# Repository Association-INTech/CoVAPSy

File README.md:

# CoVAPSy - AutoTech Project

AutoTech is a project from the INTech robotics club (Telecom SudParis and IMT Business School). Our goal is to design and build an autonomous vehicle for [CoVAPSy](https://ajuton-ens.github.io/CourseVoituresAutonomesSaclay/) (Course de Voitures Autonomes de Paris-Saclay) competition.

This repository contains the source code for our autonomous vehicle for the 2025 and 2026 competitions.

## Our Approach

We chose to use a full Reinforcement Learning approach. We train an agent to drive the vehicle in a simulation of the race based directly on sensor inputs.

We train the AI model in parallel remote environments through nammed pipes connections between the main python script and the multiple webots instances.

Inside the simulations, each vehicle has access to data comming from a LiDAR and a camera.

- Simulator: [Webots](https://cyberbotics.com/)
- AI Training Library: [Stable-Baselines3](https://stable-baselines3.readthedocs.io/en/master/) with a [Pytorch](https://pytorch.org/) backend
- AI Inference Engine: [ONNX](https://onnx.ai/)

## Installation

We use uv for Python environment management. So if it's not already installed go check the [official installation guide](https://docs.astral.sh/uv/getting-started/installation/)

Then, just `uv sync` to create the virtual environment and get all the dependencies.
```bash
# dependencies for AI training
uv sync --extra simu

# dependencies for AI inference on the Raspberry PI 5
uv sync --extra rpi
```

## Training usage

Navigate to the simulator directory.
```bash
cd src/Simulateur
```

Run the multi-process training script.
```bash
uv run launch_train_multiprocessing.py
```
This will launch the Webots instances and begin the SB3 PPO training loop. All the checkpoints will be in the `checkpoints` directory. At every checkpoint, a compiled ONNX model will be stored as `model.onnx`.

To change the parameters of the simulation, just modify the `config.py` file.

## Inference usage

(WIP)

# Wiki (Documentation)

For detailed information on architecture, hardware specifics and technical choices, please refer to the [INTech wiki](https://wiki.intech-robotics.fr).

(Note: The Wiki is currently private and reserved to INTech members)

# some dependencies needed 
libcap-dev
python3-libcamera

# License

This project is distributed under the MIT License. See the Licence file for details.

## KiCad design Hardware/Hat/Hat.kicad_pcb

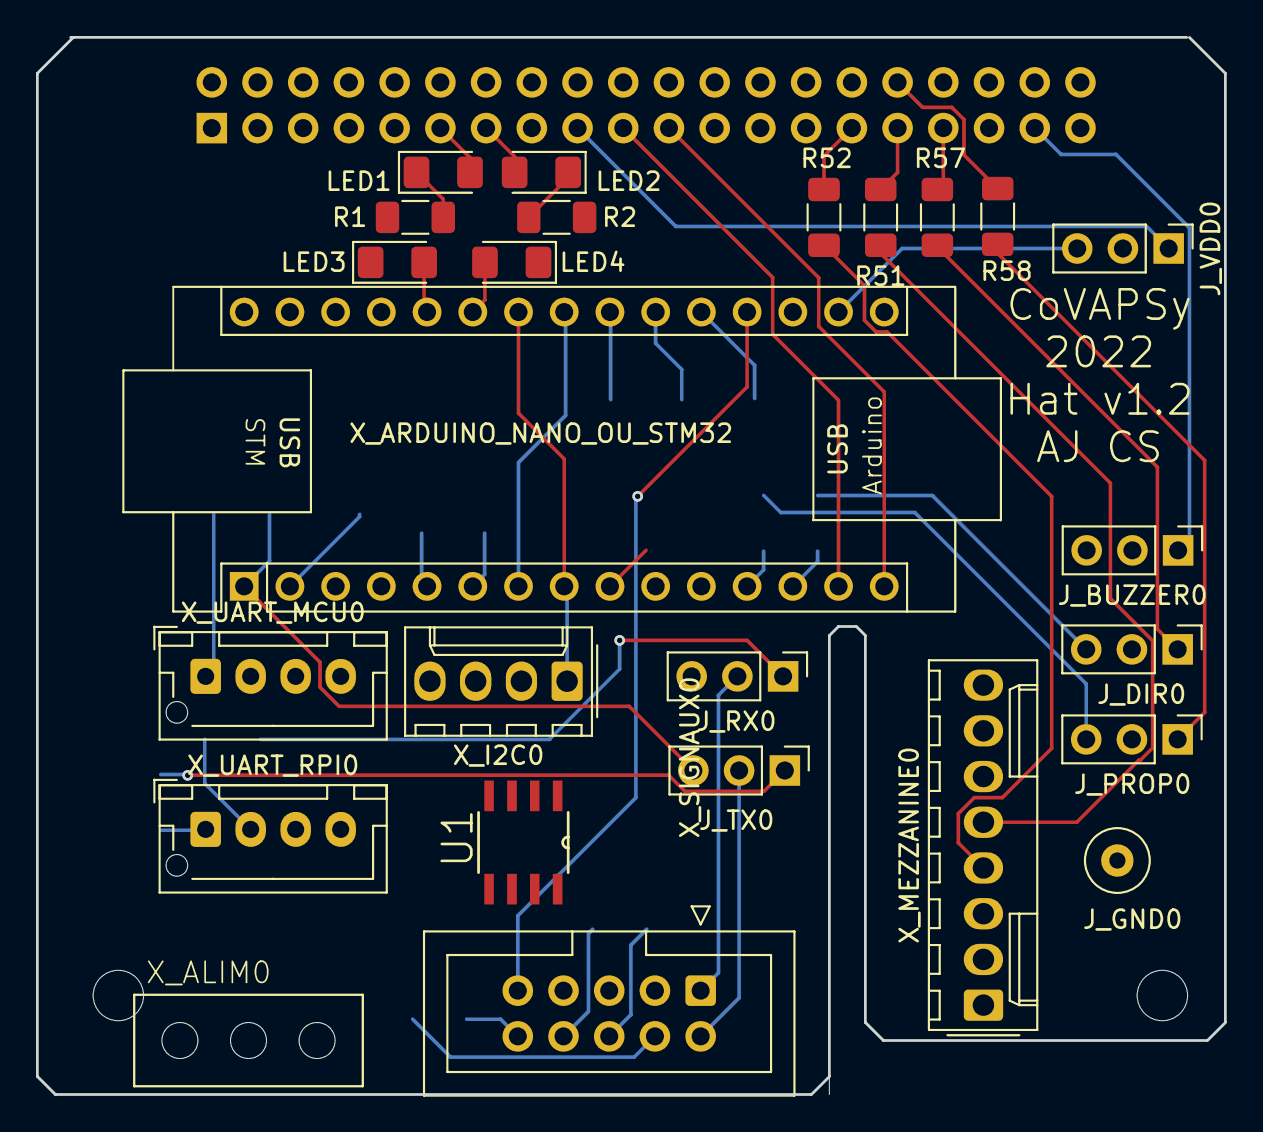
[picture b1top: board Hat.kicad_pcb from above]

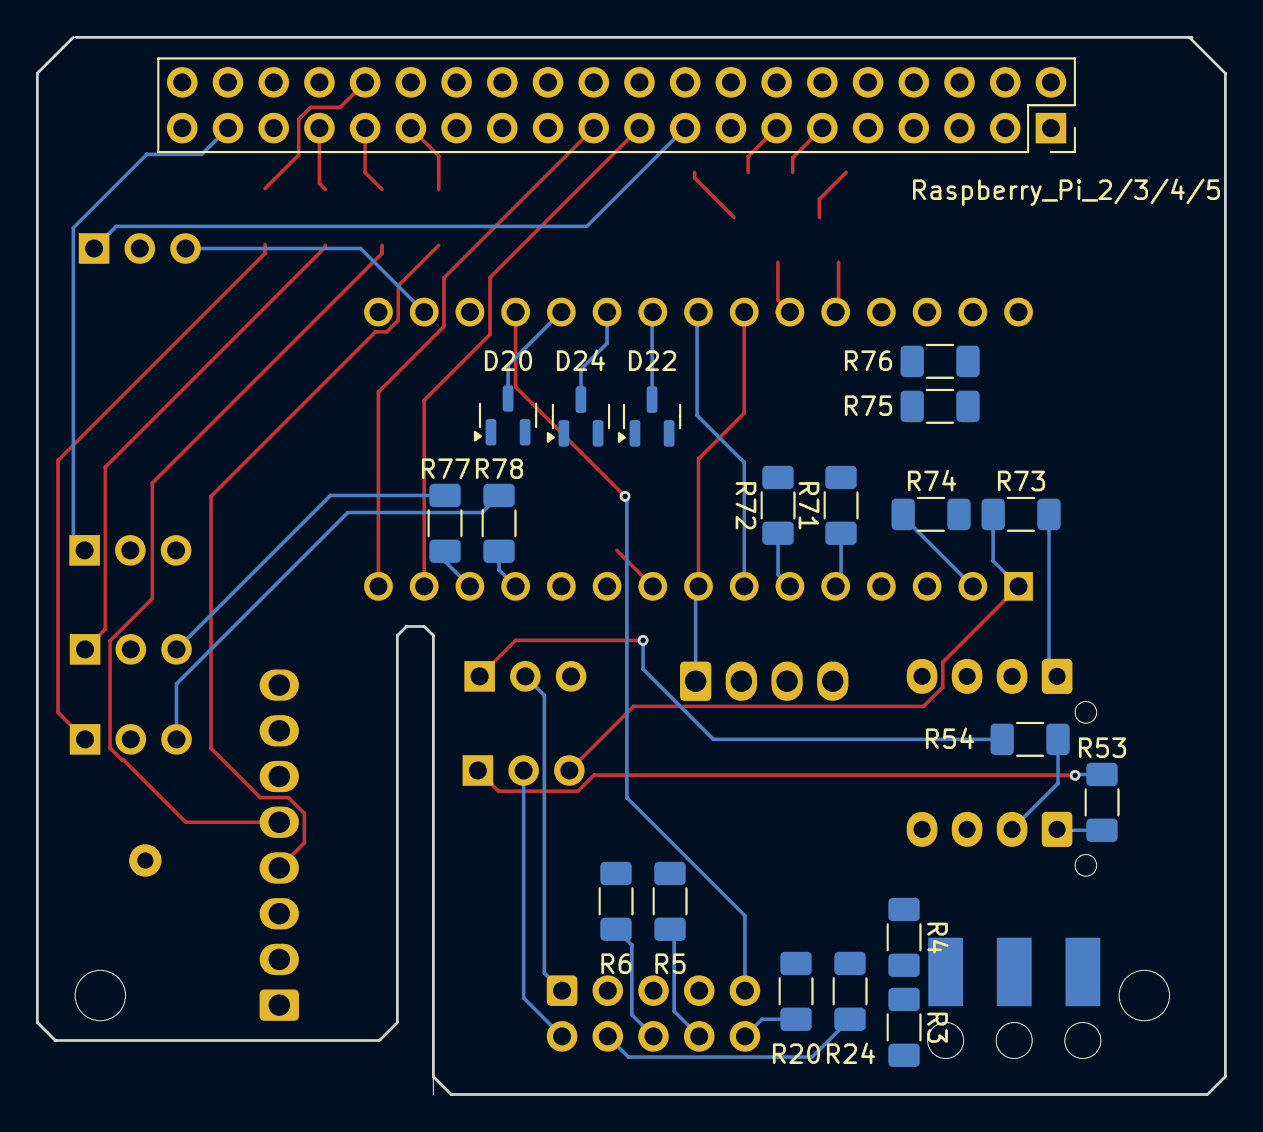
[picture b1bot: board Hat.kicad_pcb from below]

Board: 2 copper layers, 66.0 x 58.7 mm, 47 parts (20 on the bottom side), 56 nets.

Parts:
@HOLE0, @HOLE1: (no value)
D20, D22, D24: BAT54S; SOT-23
J_BUZZER0: Jumper_3_Open; PinHeader_1x03_P2.54mm_Vertical
J_DIR0: Jumper_3_Open; PinHeader_1x03_P2.54mm_Vertical
J_GND0: TestPoint; TestPoint_Loop_D3.50mm_Drill0.9mm_Beaded
J_PROP0: Jumper_3_Open; PinHeader_1x03_P2.54mm_Vertical
J_RX0: Jumper_3_Open; PinHeader_1x03_P2.54mm_Vertical
J_TX0: Jumper_3_Open; PinHeader_1x03_P2.54mm_Vertical
J_VDD0: Jumper_3_Open; PinHeader_1x03_P2.54mm_Vertical
LED1, LED2, LED3, LED4: LEDSML1206; D_1206_3216Metric_Pad1.42x1.75mm_HandSolder
R1, R2, R3, R20, R24, R51, R52, R53, R54, R57, R58, R71, R72, R73, R74, R75, R76, R77, R78: 560; R_1206_3216Metric_Pad1.30x1.75mm_HandSolder
R4: 1k; R_1206_3216Metric_Pad1.30x1.75mm_HandSolder
R5, R6: 4.7k; R_1206_3216Metric_Pad1.30x1.75mm_HandSolder
Raspberry_Pi_2/3/4/5: Conn_02x20; PinHeader_2x20_P2.54mm_Vertical
U1: PCA9517D; SOIC127P600X175-8N
X_ALIM0: CONN_ALIM_3TROUS
X_ARDUINO_NANO_OU_STM32: ARDUINO_NANO_STM32_NUCLEO; Arduino_Nano
X_I2C0: Conn_01x04; Molex_KK-254_AE-6410-04A_1x04_P2.54mm_Vertical
X_MEZZANINE0: Molex_KK-254_AE-6410-08A_1x08_P2.54mm_Vertical
X_SIGNAUX0: Conn_02x05; IDC-Header_2x05_P2.54mm_Vertical
X_UART_MCU0: Conn_01x04; JST_XH_B4B-XH-AM_1x04_P2.50mm_Vertical
X_UART_RPI0: Conn_01x04; JST_XH_B4B-XH-AM_1x04_P2.50mm_Vertical

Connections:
/BP1: R52.2, R71.2, X_MEZZANINE0.4
/BP2: R51.2, R72.2, X_MEZZANINE0.5
/BUZZER: J_BUZZER0.2 (C), X_MEZZANINE0.8
/BUZZER_MCU: J_BUZZER0.3 (B), X_ARDUINO_NANO_OU_STM32.9 (D6)
/BUZZER_RPI: J_BUZZER0.1 (A), Raspberry_Pi_2/3/4/5.37 (GPIO26)
/CAPT_IR_G: D20.3 (COM), R20.2, X_ARDUINO_NANO_OU_STM32.20 (A1)
/FOURCHE: X_ARDUINO_NANO_OU_STM32.19 (A0), X_SIGNAUX0.9
/I2C_SCL: Raspberry_Pi_2/3/4/5.5 (SCL/GPIO3), U1.2 (SCLA), X_ARDUINO_NANO_OU_STM32.8 (D5), X_ARDUINO_NANO_OU_STM32.24 (A5), X_I2C0.1, X_MEZZANINE0.3
/I2C_SCL_5V: R6.2, U1.7 (SCLB), X_SIGNAUX0.6
/I2C_SDA: Raspberry_Pi_2/3/4/5.3 (SDA/GPIO2), U1.3 (SDAA), X_ARDUINO_NANO_OU_STM32.7 (D4), X_ARDUINO_NANO_OU_STM32.23 (A4), X_I2C0.2, X_MEZZANINE0.2
/I2C_SDA_5V: R5.1, U1.6 (SDAB), X_SIGNAUX0.8
/MESURE_VBAT_LiPo: D24.3 (COM), R24.1, R24.2, X_ARDUINO_NANO_OU_STM32.21 (A2), X_SIGNAUX0.4
/MESURE_VBAT_NiMH: D22.3 (COM), X_ARDUINO_NANO_OU_STM32.22 (A3)
/MISO: Raspberry_Pi_2/3/4/5.21 (MISO0/GPIO9), X_ARDUINO_NANO_OU_STM32.15 (D12)
/MOSI: Raspberry_Pi_2/3/4/5.19 (MOSI0/GPIO10), X_ARDUINO_NANO_OU_STM32.14 (D11)
/PROPULSION_MCU: J_PROP0.3 (B), R78.2
/PROPULSION_RPI: J_PROP0.1 (A), R58.2
/PWM_DIRECTION: J_DIR0.2 (C), X_SIGNAUX0.5
/PWM_PROPULSION: J_PROP0.2 (C), X_SIGNAUX0.3
/RESET: X_ARDUINO_NANO_OU_STM32.3 (~RESET), X_MEZZANINE0.6
/RX_DIR: J_RX0.2 (C), X_SIGNAUX0.1
/RX_MCU: J_RX0.3 (B), R74.1, X_ARDUINO_NANO_OU_STM32.2 (D0/RX)
/RX_MCU_P: R74.2, X_UART_MCU0.2
/RX_RPI: J_RX0.1 (A), R54.1, Raspberry_Pi_2/3/4/5.10 (GPIO15/RXD)
/RX_RPI_P: R54.2, X_UART_RPI0.2
/SCK: Raspberry_Pi_2/3/4/5.23 (SCLK0/GPIO11), X_ARDUINO_NANO_OU_STM32.16 (D13)
/SERVO_DIR_MCU: J_DIR0.3 (B), R77.2
/SERVO_DIR_RPI: J_DIR0.1 (A), R57.2
/TELEM_G: R20.1, X_SIGNAUX0.10
/TX_DIR: J_TX0.2 (C), X_SIGNAUX0.2
/TX_MCU: J_TX0.3 (B), R73.1, X_ARDUINO_NANO_OU_STM32.1 (D1/TX)
/TX_MCU_P: R73.2, X_UART_MCU0.1
/TX_RPI: J_TX0.1 (A), R53.1, Raspberry_Pi_2/3/4/5.8 (GPIO14/TXD)
/TX_RPI_P: R53.2, X_UART_RPI0.1
/VCC_5V: R5.2, R6.1, Raspberry_Pi_2/3/4/5.2 (5V), Raspberry_Pi_2/3/4/5.4 (5V), U1.8 (VCCB), X_ARDUINO_NANO_OU_STM32.27 (+5V)
/VDD_MCU: J_VDD0.3 (B), X_ARDUINO_NANO_OU_STM32.17 (3V3)
/VDD_RPI: J_VDD0.1 (A), Raspberry_Pi_2/3/4/5.17 (3V3)
GND: D20.1 (A), D22.1 (A), D24.1 (A), J_GND0.1, R1.2, R2.2, R3.2, R75.2, R76.2, Raspberry_Pi_2/3/4/5.6 (GND), Raspberry_Pi_2/3/4/5.9 (GND), Raspberry_Pi_2/3/4/5.14 (GND), Raspberry_Pi_2/3/4/5.20 (GND), Raspberry_Pi_2/3/4/5.25 (GND), Raspberry_Pi_2/3/4/5.30 (GND), Raspberry_Pi_2/3/4/5.34 (GND), Raspberry_Pi_2/3/4/5.39 (GND), U1.4 (GND), X_ALIM0.P$2, X_ARDUINO_NANO_OU_STM32.4 (GND), X_ARDUINO_NANO_OU_STM32.29 (GND), X_I2C0.4, X_MEZZANINE0.7, X_UART_MCU0.3, X_UART_RPI0.3
unnamed: LED1.2 (A), Raspberry_Pi_2/3/4/5.11 (GPIO17)
unnamed: LED1.1 (K), R1.1
unnamed: LED2.2 (A), Raspberry_Pi_2/3/4/5.13 (GPIO27)
unnamed: LED2.1 (K), R2.1
unnamed: LED3.2 (A), X_ARDUINO_NANO_OU_STM32.26 (A7)
unnamed: LED3.1 (K), R76.1
unnamed: LED4.2 (A), X_ARDUINO_NANO_OU_STM32.25 (A6)
unnamed: LED4.1 (K), R75.1
unnamed: R3.1, R4.2
unnamed: R52.1, Raspberry_Pi_2/3/4/5.29 (GCLK1/GPIO5)
unnamed: R51.1, Raspberry_Pi_2/3/4/5.31 (GCLK2/GPIO6)
unnamed: R58.1, Raspberry_Pi_2/3/4/5.32 (PWM0/GPIO12)
unnamed: R57.1, Raspberry_Pi_2/3/4/5.33 (PWM1/GPIO13)
unnamed: R71.1, X_ARDUINO_NANO_OU_STM32.5 (D2)
unnamed: R72.1, X_ARDUINO_NANO_OU_STM32.6 (D3)
unnamed: R78.1, X_ARDUINO_NANO_OU_STM32.12 (D9)
unnamed: R77.1, X_ARDUINO_NANO_OU_STM32.13 (D10)
VDD: D20.2 (K), D22.2 (K), D24.2 (K), J_VDD0.2 (C), U1.1 (VCCA), X_I2C0.3, X_MEZZANINE0.1, X_SIGNAUX0.7, X_UART_MCU0.4, X_UART_RPI0.4

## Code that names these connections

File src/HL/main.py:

# States
# 0 - Idle
# 1 - Auto Driving
# 2 - Manual Driving with ps4 controller

from gpiozero import LED, Button, Buzzer
from luma.core.interface.serial import i2c
from luma.core.render import canvas
from luma.oled.device import ssd1306
from PIL import Image, ImageDraw, ImageFont
import struct
import smbus  # type: ignore #ignore the module could not be resolved error because it is a linux only module
import textwrap

from get_ip import get_ip, check_ssh_connections

from multiprocessing import Processus #pour pouvoir lancer les programme sur un cpu différent

bus = smbus.SMBus(1)  # 1 indicates /dev/i2c-1
#oled
serial = i2c(port=1, address=0x3C)
device = ssd1306(serial)

auto_driving_p = Process(target=Auto_Driving)
manual_driving_p = Process(target=Manual_Driving)

list_p = [auto_driving_p,manual_driving_p] #liste tout les processus possible

SLAVE_ADDRESS = 0x08  # I2C address of the slave arduino or stm32
bp_next = Button("GPIO5", bounce_time=0.1)
bp_entre = Button("GPIO6", bounce_time=0.1)
led1 = LED("GPIO17")
led2 = LED("GPIO27")
buzzer = Buzzer("GPIO26")
State = 0
Screen = 0
TEXT_HEIGHT = 11
TEXT_LEFT_OFFSET = 3 # Offset from the left of the screen to ensure no cuttoff


def make_voltage_im():
    try: #Will fail if arduino is rest ex: temporary power loss when plugu=ing in usb
        received = read_data(2)  # Adjust length as needed
    except OSError:
        received = [0.0, 0.0]
        print("I2C bus error")
    
    # filter out values below 6V and round to 2 decimal places
    received = [round(elem, 2) if elem > 6 else 0.0 for elem in received]
    text = f"LiP:{received[0]:.2f}V|NiH:{received[1]:.2f}V"
    im = Image.new("1", (128, TEXT_HEIGHT), "black")
    draw = ImageDraw.Draw(im)
    font = ImageFont.load_default()
    draw.text((3, 0), text, fill="white", font=font)
    return im

def display_combined_im(text):
    im = Image.new("1", (128, 64), "black")
    draw = ImageDraw.Draw(im)
    font = ImageFont.load_default()
    
    # Wrap the text to fit within the width of the display
    wrapped_text = textwrap.fill(text, width=20)  # Adjust width as needed
    draw.text((3, 0), wrapped_text, fill="white", font=font)
    
    voltage_im = make_voltage_im()
    im.paste(voltage_im, (0, 64 - TEXT_HEIGHT))
    
    with canvas(device) as draw:
        draw.bitmap((0, 0), im, fill="white")

def write_data(float_data):
    # Convert the float to bytes
    print(float_data)
    byte_data = struct.pack('f', float_data)
    # Convert the bytes to a list of integers
    int_data = list(byte_data)
    print(int_data)
    int_data.append(0)
    # Write the data to the I2C bus
    bus.write_i2c_block_data(SLAVE_ADDRESS, int_data[0], int_data[1:4])

def read_data(num_floats=3):

    # Each float is 4 bytes
    length = num_floats * 4
    # Read a block of data from the slave
    data = bus.read_i2c_block_data(SLAVE_ADDRESS, 0, length)
    # Convert the byte data to floats
    if len(data) >= length:
        float_values = struct.unpack('f' * num_floats, bytes(data[:length]))
        return list(float_values)
    else:
        raise ValueError("Not enough data received from I2C bus")


def Idle(): #Enable chossing between states
    global Screen
    global State
    if Screen==0 and check_ssh_connections():
        led1.on()
        Screen=1
    if not check_ssh_connections():
        led1.off()
    match Screen: #Display on OLED
        case 0: #IP and ssh status
            ip=get_ip()
            text = "Ready to SSH\nIP:"+ip
        case 1: #AutoDriving mode
            text = "Auto Driving"
        case 2: #Manual Driving mode
            text = "Manual Driving With PS4 Controller"
            #PS4 controller status
        case 3: #Kill all processus
            text = "Kill all the process"
    
    if (State==Screen):
        text+=": (en cours)"

    display_combined_im(text)


    if bp_next.is_pressed:
        bp_next.wait_for_release()
        Screen+=1
        if Screen>len(list_p):
            Screen=0
    if bp_entre.is_pressed:
        bp_entre.wait_for_release() 
        State=Screen
        p_choisie(State-1) # -1 because of the process cases begin at 1 and the list_p indexe at 0

def p_choisie(p_id):
    """ Kill tout les processus et lance celui choisie par p_id dans la liste list_p
        (Donner un p_id plus grand que len(list_p) tue tout les processus
    """
    for i in range(len(list_p)):
        if (i!= p_id):
            list_p[i].terminate()

    if (p_id<len(list_p)): #vérifie que le p_id soit valide dans
        if not list_[p_id].is_alive(): #evite de relancer le programme si déjà selectionée
            list_p[p_id].start()


def Auto_Driving():
    global State
    try:
        if Driving_has_not_started:
            from Car import Car
            GR86 = Car()
        GR86.main()
        if bp_entre.is_pressed or bp_next.is_pressed:
            raise KeyboardInterrupt
    except KeyboardInterrupt:
        GR86.stop()
        Driving_has_not_started = False
        State=0
        
        
def Manual_Driving():
    global State
    print("Manual Driving")
    State=0

def main():
    while True:
        Idle()
            
        
if __name__ == "__main__":
    main()

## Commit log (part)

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2025-11-05 fix: changement dans received pour récupéré les element via read_data
2025-11-05 changement pour teste le reception des packet
2025-11-05 rest
2025-11-06 install party test lidar
2025-11-06 relol
2025-11-06 finfi?
2025-11-06 creation de test_serveur pour tester la communication zerorpc
2025-11-06 enlevage de blocking call dans le recule car géré par l'asservissement maintenant
2025-11-08 feat: rajout d'une commande d'arret lorsque je lache les manette
2025-11-08 fix : correction dans les fonctions realease avec value qui ne devrais pas être la
2025-11-12 feat : debug soucis de direction
2025-11-12 feat: rajout des constantes vitesse et direction dans la classe apivoiture
2025-11-12 feat: rajout des dépendence dans le Serveur en attendant de le rajouter dans la doc
2025-11-12 fix : self.cam.start
2025-11-12 rajout de test au début
2025-11-12 test
2025-11-13 fix : enlevage de picamera en attendant de test zerorpc
2025-11-13 changement dans test_serveur
2025-11-13 feat : enlevage des print inutile et rajout de variable pour enregistrer les état actuel de la voiture
2025-11-14 fix: fixed file names and url problem in the readme
2025-11-15 fix: fix dans serveur_mq et test_serveur
2025-11-15 rajout de sécurité pour Serveur_mq et l'envoie par i2c
2025-11-15 fix: erreur de syntaxe
2025-11-15 test de rajoue d'information dans Serveur_mq
2025-11-16 fix : changement dans Serveur_mq et creation d'un main dans Serveur_mq
2025-11-17 feat : commit (rajout de test pour le chunk de idiams
2025-11-17 fix : changement dans commande_PS4 pour marcher avec zmq
2025-11-17 changemnet et rajout d'un afffichage de running et de capacinbilité de kill les programme (mais tout les programme)
2025-11-17 feat : cela marche
2025-11-18 fix : on essaye de connecter le reste à la pi
2025-11-18 feat : passage en sub/pub pour soucis de vitesse
2025-11-18 feat : utilisation de udp pour controller la voiture a distance
2025-11-18 fix : reimplementation de l'envoie d'info par Serveur_mq
2025-11-18 fix: chnaghement de non dans switch_remote_control
2025-11-18 feat :rajout de bouton reboot
2025-11-19 fix : reduction du lag dans la direction en envoie (j'ai supprimer le time.sleep sa fait peur mais l'arduino tank (j'éspere))
2025-11-19 fix : enleve le raise si on trouve pas le lidar
2025-11-19 fix : changement dans startup pour lancer Serveur_mq avec uv
2025-11-19 fix: résolution de l'appel de uv directement dans startup
2025-11-20 fix: fixed use psutils for macOS compatibility
2025-11-20 fix: fixed the virage on piste 0
2025-11-20 fix: on fait en sorte que lorsque l'on reapuiille sur le bouton cela relance le programme
2025-11-21 feat : rajout de fonction pas utiliser
2025-11-21 unfonctionnal: split lauch programm
2025-11-21 fix : dans uv avec les bonne dépendance
2025-11-22 fix: no more error with checkpoints dir not existing
2025-11-22 Revert "Split train"
2025-11-22 correction des selfs du C
2025-11-22 fix : fix some issues after the merge between nikopol and arthur
2025-11-22 AlmostFeat : replacing emitter / receiver by fifo. Not working
2025-11-30 rajout de Camera_serv qui lance sur un lien la camera en temps réel
2025-11-30 changement du thread de camera_serv dans serveur_mq
2025-11-30 Mathias's issues give to Nachid test 1
2025-12-01 rajouut de scipy en temps que dependance
2025-12-02 fix: petit fix sur coment son lancé les fonctions depuis le menu
2025-12-02 fix: kill du thread de remote control maintenant opérationnelle
2025-12-02 rajout, d'information a envoyé.
2025-12-04 feat: utilisation du nouveau system de programme en passant tout par des classe
2025-12-04 fix: petit embélissement et suppression de chose inutile
2025-12-04 fix: dans remote control import time
2025-12-04 fix : rajout de la possibilité de mettre la voiture en stand by.
2025-12-11 feat : rajout Car pour qu'il soit utiliser dans la nouvelle structure
2025-12-16 test: rajout d'un programme pour les module externe
2025-12-16 fix: petit soucis
2025-12-16 fix : suppression de fichier inutile
2025-12-17 fix: soucis oublie de self dans poweroff
2025-12-19 ajout dependance pas faire attention
2025-12-19 fix: revue de la structure du code (en terme de architecture des fichier avec creation de dossier et déplacement des fichiers pour plus de lisibilité du code.
2025-12-19 fix: toujours changement relatif au import
2025-12-19 feat: rajout de log partout
2025-12-26 feat : rajout de constante dans autotech constante et dans Serveur_mq pour plus de personalisation
2025-12-26 feat: rajout de constant pour le stream de la camera
2025-12-26 feat: rajout de commentaire dans Autotech_constante et suppression du fichier test_serveur qui na plus lieux d'être
2025-12-26 feat: changement pour êue le script se lace mme si il est toujours pas connecter à un réseaux et affiche sur l'écran lorsqu'il est connecté
2026-01-09 fix : petite erreur dans autotech_constante
2026-01-09 feat: rajout de git reset hard pour empecher que le pull bloque si il y aeu des modif sur les fichier dans la pi
2026-01-09 ajout du code lié au lancement d'une seul simu
2026-01-09 fix: rajout de __name__ pour les bon dire monsieur Danura
2026-01-09 fix: rajout de __main = __name pour les bon vouloir e Danura
2026-01-09 fix: this simulation and fifo work perfectly
2026-01-09 fix: fix de camera_serv car soucis lors du lancement du stream
2026-01-09 tentative d'inversion des maps
2026-01-10 fix: suppression de code inutile
2026-01-10 feat: rajout du frontend et du backend simple avec implementation du site
2026-01-10 feat : oublie de app.js oups
2026-01-10 feat: rajout de lien complet
2026-01-11 feat: rajout du lancement automatique du backend et de la camera au lancement de la voiture
2026-01-11 feat: rajout la possibilité de stream le lidar
2026-01-11 fix: petit fix dans le stream du lidar
2026-01-11 fix: fix de l'apperçue du lidar dans le site
2026-01-11 fix : fix du lidat
2026-01-11 fix : fix du lidar sur le site
2026-01-11 feat: rajout de la vitesse demander et direction demander au site
2026-01-11 rajout de websockets
2026-01-11 feat: rajout de la visualisation de la diférence entre vitesse_réel et vitesse_demander plus une visualisation de la direction
2026-01-13 fix : suppression d'un fichier inutile
2026-01-13 added some missing LFS files
2026-01-13 Revert "added some missing LFS files (#27)"
    This reverts commit 50af20900f886f6022163474a378fce9cac5abc5.
2026-01-13 Revert "added some missing LFS files (#27)" (#28)
    This reverts commit 50af20900f886f6022163474a378fce9cac5abc5.
2026-01-14 fix:passage avec un system de wobsocket pour moin de log impossible
2026-01-15 feat: Script to go backward added
2026-01-15 feat: rajout du fait que le lidar et la camera sont clicable pour pouvoir les ouvrir dans un autre onglet
2026-01-15 fix: vue pour lorsque la voiture recule
2026-01-15 fix: optimisation v2 du code.
2026-01-16 fix: merge should be working now
2026-01-23 feat: A lot of refactoring
    I changed the whole project architecture and fixed most prolbems I found
    in simulation. I still have some french to english translation to do.
    The high_level and low_level parts still have to get refactored though.
2026-01-23 fix: moved a dir
2026-01-24 fix: models and checkpoints are now saved in /tmp/autotech
2026-01-26 fix: changement des nom des variable en anglais
2026-01-26 feat: for happy matthias
2026-01-26 feat: pour le genti matthias
2026-01-27 feat: rajout du logo de autotech en haut à gauche de la page
2026-01-30 fix: some inutile stuf and move and renome another
2026-01-30 Fin du reverse des maps
2026-01-30 feat: refractor de la partie HL en high level
2026-01-30 feat: enlevage de soucis dans le toml
2026-01-31 fix: some html for more view on the backend
2026-01-31 fix: delete some inutile file
2026-02-02 fix: changed save path from /tmp to ~/.cache
    /tmp is mounted as tmpfs so remains in the ram so we should not stores
    models in it
2026-02-02 feat: test
2026-02-02 feat: rajoute de la possibilité d'avoir la camera sur le backend avec mediamtx.
2026-02-02 fix: rajout de la camera dans le programme
2026-02-05 feat: suite au commit précédents
2026-02-05 fix: delete useless models
2026-02-05 fix: the authors are now in the main pyproject.toml
2026-02-05 fix: le lidar et ça transmission
2026-02-08 fix: better way to see the state of the programs in initialisation.py
2026-02-08 feat: extractor class defines constants
2026-02-08 feat: rajout des fichier systemctl de config dans le dossier script de hl
2026-02-09 feat: refactor in english the backend
2026-02-09 fix: fix the ia for testing
2026-02-09 fix: fixed A LOT of ruff warnings
2026-02-11 feat: rajout de la possibilité de choisir le model dans le dossier correspondant (il faut encore changer backend pour marcher avec la nouvelle architecture
2026-02-11 fix: update du code pour marrcher avec le nouveau tof VLX53L1X
2026-02-11 feat: modif pour que le programme prenne que deux carte sur le site
2026-02-11 feat: rajout de la vue du tof sur la pov du lidar
2026-02-11 feat: rajout du tof operationnelle sur le site
2026-02-12 fix: corection d'erreur de typage
2026-02-14 feat: rajout de tof dans le backend
2026-02-17 feat: déplacage du calcule des coordonner cartésienne dans le clients et non sur la pi
2026-02-17 fix: lidar big view and the car border
2026-02-17 feat: rajout de truc pour debug
2026-02-17 fix: refactored some snake vs camel vs pascal case names
2026-02-17 fix: changed Program fields to properties
2026-02-17 fix: translated A LOT of french to english
2026-02-17 fix: deleted unused uv.lock
2026-02-17 fix: some property were missing
2026-02-18 fix merging of all with some refactor and fix some error of naming
2026-02-25 feat: rajout de la fonction has_crashed aqui utilise le lidar
2026-02-28 fix: cannot import name '_RetAddress' from '_socket' (unknown location)
2026-02-28 fix: some issus on the crashed implementation
2026-03-01 feat: petit changement pour plus de lisibilité
2026-03-01 feat: rajout d'une classe qui regarde si la voiture tourne en reverse (and deleting some inutilie file and refactording for the driver doc)
2026-03-01 fix: deleting actionneur_capteur doc and refactoring for using driver instead
2026-03-01 feat: adding a debbuging of what the ai see
2026-03-02 feat: driver -> drivers
2026-03-10 feat: adding a proxy for paying the camera script into a subprocess because of some error when playing with the others scripts
2026-03-14 Try d'implementer launch_one_simu dans le refactoring 2
2026-03-14 feat: removing on camera some function to avoid double function on CameraProxy and Camera. (and changing some stuff according to the new use case of camera_proxy
2026-03-14 feat: adding some cleaning if the link existed before for shared memory on camera
2026-03-14 feat: ddinig some stop on the camera for cleaning things
2026-03-14 feat: addinig callback for a clean ending of the code
2026-03-15 fix: fixinig some error and logic in launching ia
2026-03-19 Fix : lanch_one_simu.py marche a un peu. Mais Crash au bout de 3 collisions. Je ne trouve pas pk
2026-03-19 Fix : lanch_one_simu.py marche a 100% je crois Je le prie actuellement
2026-03-19 feat test de fou
2026-03-20 fix: some code for chosing how to run the ai
2026-03-20 fix: moved ai hyperparameters to config.py
2026-03-22 fix: some change in managing thye ip adresse
2026-03-22 fix:some ia fitures
2026-03-23 feat: fixing some issue with the ai
2026-03-24 feat: we can choose to go backwards or respawn when crashing
    I also move some stuff to config.py
2026-03-24 fix: forgot the .__name__
2026-03-26 feat: testing asserv2bazar change
2026-04-08 feat?: no camera should be working but it doesn't idk why
2026-04-10 fix : some things and ia
2026-04-11 fix : sa marche (je croit
2026-04-11 fix: for the competition:!!!
2026-04-23 fix: some imports that were wrong or too complicated
2026-04-25 fix: no more deadlock
    the problem was that np defautls to flaot64 and I use float32 everywhere
    else so when concatenating it with the other vectors, the whole thing
    becomes np.float64. This would create a 4 bytes offset for each element of
    the vector at each reset.
    This would destroy the order of elements and fill the pipe up until it
    reaches the max size.
2026-04-27 rm uv.lock
2026-05-01 feat: models use in the competition covapsy 2026
